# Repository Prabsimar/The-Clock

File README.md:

# The-Clock
A clock made using arduino and pcb designing

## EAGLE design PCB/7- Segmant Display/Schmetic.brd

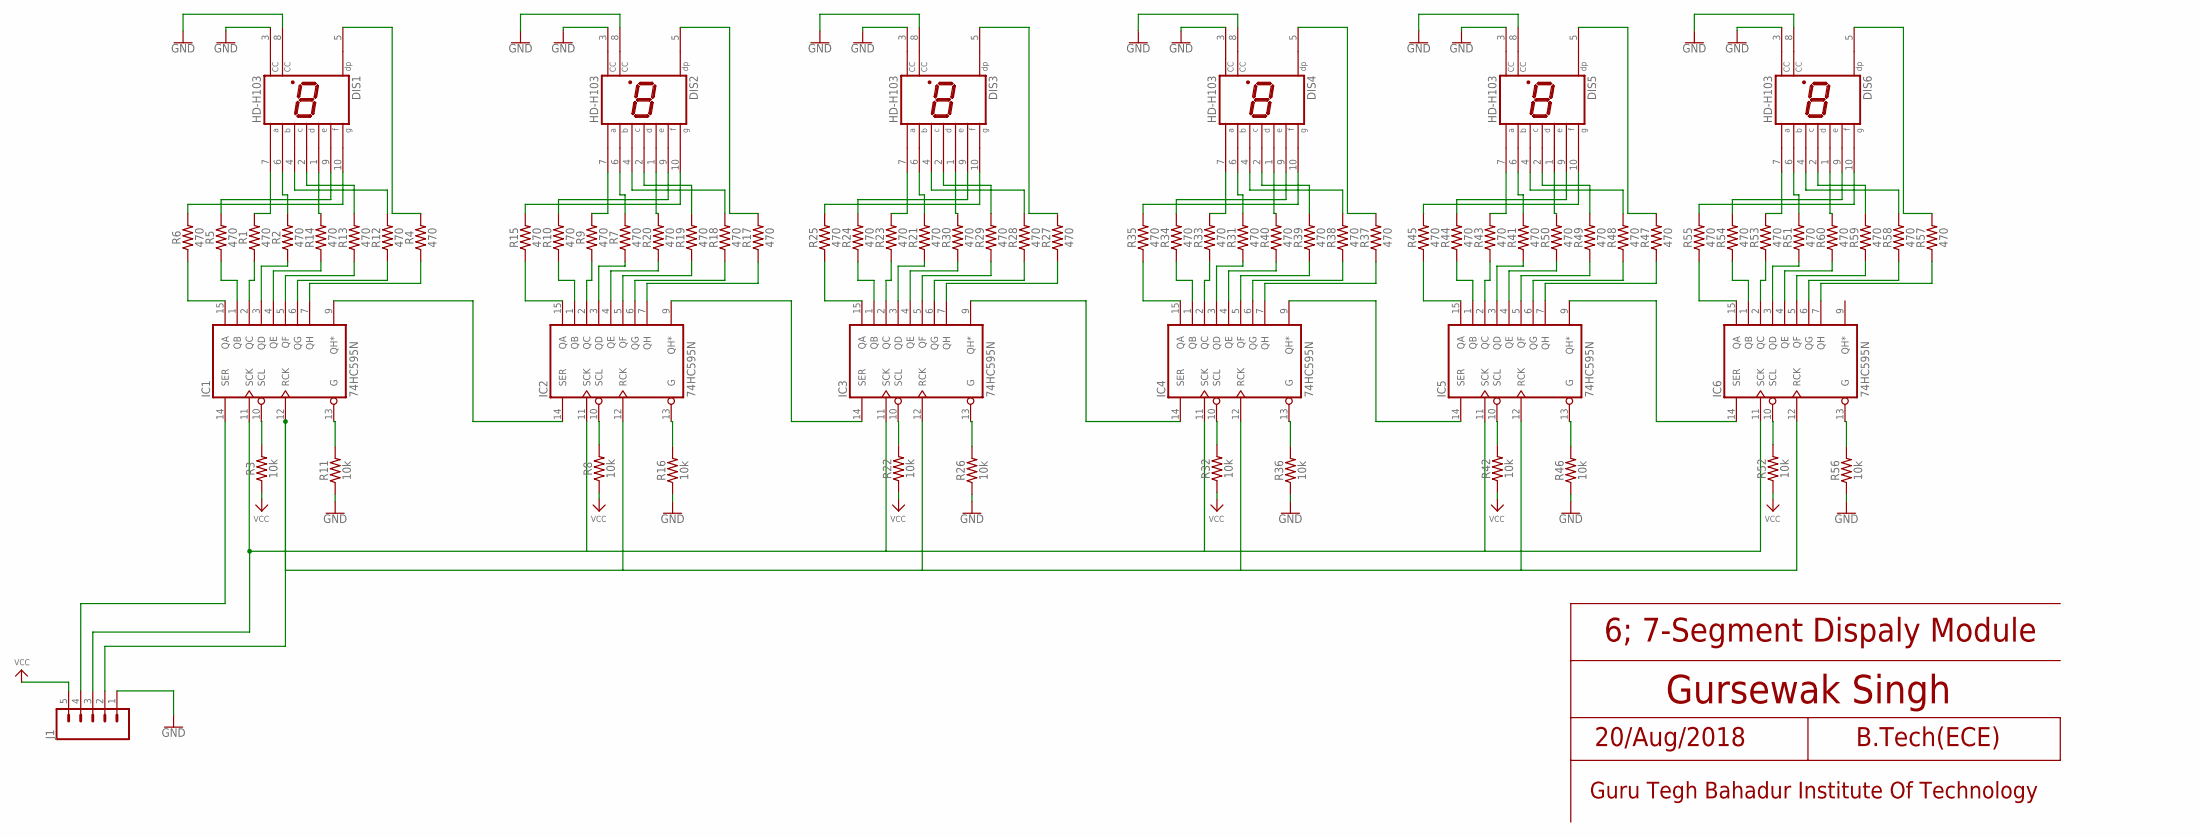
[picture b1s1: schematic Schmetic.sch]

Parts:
DIS1, DIS2, DIS3, DIS4, DIS5, DIS6: HD-H103; HDSP-M
IC1, IC2, IC3, IC4, IC5, IC6: 74HC595N; DIL16
J1: CONN_05LOCK_LONGPADS; 1X05_LOCK_LONGPADS
R1, R2, R4, R5, R6, R7, R9, R10, R12, R13, R14, R15, R17, R18, R19, R20, R21, R23, R24, R25, R27, R28, R29, R30, R31, R33, R34, R35, R37, R38, R39, R40, R41, R43, R44, R45, R47, R48, R49, R50, R51, R53, R54, R55, R57, R58, R59, R60: 470; AXIAL-0.3
R3, R8, R11, R16, R22, R26, R32, R36, R42, R46, R52, R56: 10k; AXIAL-0.3

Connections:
GND: DIS1.3 (CC), DIS1.8 (CC), DIS2.3 (CC), DIS2.8 (CC), DIS3.3 (CC), DIS3.8 (CC), DIS4.3 (CC), DIS4.8 (CC), DIS5.3 (CC), DIS5.8 (CC), DIS6.3 (CC), DIS6.8 (CC), IC1.8 (GND), IC2.8 (GND), IC3.8 (GND), IC4.8 (GND), IC5.8 (GND), IC6.8 (GND), J1.1, R11.P$1 (1), R16.P$1 (1), R26.P$1 (1), R36.P$1 (1), R46.P$1 (1), R56.P$1 (1)
unnamed: IC1.15 (QA), R6.P$1 (1)
unnamed: IC1.1 (QB), R5.P$1 (1)
unnamed: IC1.2 (QC), R1.P$1 (1)
unnamed: IC1.3 (QD), R2.P$1 (1)
unnamed: IC1.4 (QE), R14.P$1 (1)
unnamed: IC1.5 (QF), R13.P$1 (1)
unnamed: IC1.6 (QG), R12.P$1 (1)
unnamed: IC1.7 (QH), R4.P$1 (1)
unnamed: DIS1.10 (G), R6.P$2 (2)
unnamed: DIS1.9 (F), R5.P$2 (2)
unnamed: DIS1.7 (A), R1.P$2 (2)
unnamed: DIS1.6 (B), R2.P$2 (2)
unnamed: DIS1.1 (E), R14.P$2 (2)
unnamed: DIS1.2 (D), R13.P$2 (2)
unnamed: DIS1.4 (C), R12.P$2 (2)
unnamed: DIS1.5 (DP), R4.P$2 (2)
unnamed: IC2.15 (QA), R15.P$1 (1)
unnamed: IC1.10 (SCL), R3.P$2 (2)
unnamed: IC1.13 (G), R11.P$2 (2)
unnamed: IC2.1 (QB), R10.P$1 (1)
unnamed: IC2.2 (QC), R9.P$1 (1)
unnamed: IC2.3 (QD), R7.P$1 (1)
unnamed: IC2.4 (QE), R20.P$1 (1)
unnamed: IC2.5 (QF), R19.P$1 (1)
unnamed: IC2.6 (QG), R18.P$1 (1)
unnamed: IC2.7 (QH), R17.P$1 (1)
unnamed: DIS2.10 (G), R15.P$2 (2)
unnamed: DIS2.9 (F), R10.P$2 (2)
unnamed: DIS2.7 (A), R9.P$2 (2)
unnamed: DIS2.6 (B), R7.P$2 (2)
unnamed: DIS2.1 (E), R20.P$2 (2)
unnamed: DIS2.2 (D), R19.P$2 (2)
unnamed: DIS2.4 (C), R18.P$2 (2)
unnamed: DIS2.5 (DP), R17.P$2 (2)
unnamed: IC2.10 (SCL), R8.P$2 (2)
unnamed: IC2.13 (G), R16.P$2 (2)
unnamed: IC3.15 (QA), R25.P$1 (1)
unnamed: IC3.1 (QB), R24.P$1 (1)
unnamed: IC3.2 (QC), R23.P$1 (1)
unnamed: IC3.3 (QD), R21.P$1 (1)
unnamed: IC3.4 (QE), R30.P$1 (1)
unnamed: IC3.5 (QF), R29.P$1 (1)
unnamed: IC3.6 (QG), R28.P$1 (1)
unnamed: IC3.7 (QH), R27.P$1 (1)
unnamed: DIS3.10 (G), R25.P$2 (2)
unnamed: DIS3.9 (F), R24.P$2 (2)
unnamed: DIS3.7 (A), R23.P$2 (2)
unnamed: DIS3.6 (B), R21.P$2 (2)
unnamed: DIS3.1 (E), R30.P$2 (2)
unnamed: DIS3.2 (D), R29.P$2 (2)
unnamed: DIS3.4 (C), R28.P$2 (2)
unnamed: DIS3.5 (DP), R27.P$2 (2)
unnamed: IC3.10 (SCL), R22.P$2 (2)
unnamed: IC3.13 (G), R26.P$2 (2)
unnamed: IC4.15 (QA), R35.P$1 (1)
unnamed: IC4.1 (QB), R34.P$1 (1)
unnamed: IC4.2 (QC), R33.P$1 (1)
unnamed: IC4.3 (QD), R31.P$1 (1)
unnamed: IC4.4 (QE), R40.P$1 (1)
unnamed: IC4.5 (QF), R39.P$1 (1)
unnamed: IC4.6 (QG), R38.P$1 (1)
unnamed: IC4.7 (QH), R37.P$1 (1)
unnamed: DIS4.10 (G), R35.P$2 (2)
unnamed: DIS4.9 (F), R34.P$2 (2)
unnamed: DIS4.7 (A), R33.P$2 (2)
unnamed: DIS4.6 (B), R31.P$2 (2)
unnamed: DIS4.1 (E), R40.P$2 (2)
unnamed: DIS4.2 (D), R39.P$2 (2)
unnamed: DIS4.4 (C), R38.P$2 (2)
unnamed: DIS4.5 (DP), R37.P$2 (2)
unnamed: IC4.10 (SCL), R32.P$2 (2)
unnamed: IC4.13 (G), R36.P$2 (2)
unnamed: IC5.15 (QA), R45.P$1 (1)
unnamed: IC5.1 (QB), R44.P$1 (1)
unnamed: IC5.2 (QC), R43.P$1 (1)
unnamed: IC5.3 (QD), R41.P$1 (1)
unnamed: IC5.4 (QE), R50.P$1 (1)
unnamed: IC5.5 (QF), R49.P$1 (1)
unnamed: IC5.6 (QG), R48.P$1 (1)
unnamed: IC5.7 (QH), R47.P$1 (1)
unnamed: DIS5.10 (G), R45.P$2 (2)
unnamed: DIS5.9 (F), R44.P$2 (2)
unnamed: DIS5.7 (A), R43.P$2 (2)
unnamed: DIS5.6 (B), R41.P$2 (2)
unnamed: DIS5.1 (E), R50.P$2 (2)
unnamed: DIS5.2 (D), R49.P$2 (2)
unnamed: DIS5.4 (C), R48.P$2 (2)
unnamed: DIS5.5 (DP), R47.P$2 (2)
unnamed: IC5.10 (SCL), R42.P$2 (2)
unnamed: IC5.13 (G), R46.P$2 (2)
unnamed: IC6.15 (QA), R55.P$1 (1)
unnamed: IC6.1 (QB), R54.P$1 (1)
unnamed: IC6.2 (QC), R53.P$1 (1)
unnamed: IC6.3 (QD), R51.P$1 (1)
unnamed: IC6.4 (QE), R60.P$1 (1)
unnamed: IC6.5 (QF), R59.P$1 (1)
unnamed: IC6.6 (QG), R58.P$1 (1)
unnamed: IC6.7 (QH), R57.P$1 (1)
unnamed: DIS6.10 (G), R55.P$2 (2)
unnamed: DIS6.9 (F), R54.P$2 (2)
unnamed: DIS6.7 (A), R53.P$2 (2)
unnamed: DIS6.6 (B), R51.P$2 (2)
unnamed: DIS6.1 (E), R60.P$2 (2)
unnamed: DIS6.2 (D), R59.P$2 (2)
unnamed: DIS6.4 (C), R58.P$2 (2)
unnamed: DIS6.5 (DP), R57.P$2 (2)
unnamed: IC6.10 (SCL), R52.P$2 (2)
unnamed: IC6.13 (G), R56.P$2 (2)
unnamed: IC1.9 (QH*), IC2.14 (SER)
unnamed: IC2.9 (QH*), IC3.14 (SER)
unnamed: IC3.9 (QH*), IC4.14 (SER)
unnamed: IC4.9 (QH*), IC5.14 (SER)
unnamed: IC5.9 (QH*), IC6.14 (SER)
unnamed: IC1.11 (SCK), IC2.11 (SCK), IC3.11 (SCK), IC4.11 (SCK), IC5.11 (SCK), IC6.11 (SCK), J1.3
unnamed: IC1.12 (RCK), IC2.12 (RCK), IC3.12 (RCK), IC4.12 (RCK), IC5.12 (RCK), IC6.12 (RCK), J1.2
unnamed: IC1.14 (SER), J1.4
VCC: IC1.16 (VCC), IC2.16 (VCC), IC3.16 (VCC), IC4.16 (VCC), IC5.16 (VCC), IC6.16 (VCC), J1.5, R3.P$1 (1), R8.P$1 (1), R22.P$1 (1), R32.P$1 (1), R42.P$1 (1), R52.P$1 (1)

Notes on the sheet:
6; 7-Segment Dispaly Module
Gursewak Singh
20/Aug/2018
B.Tech(ECE)
Guru Tegh Bahadur Institute Of Technology

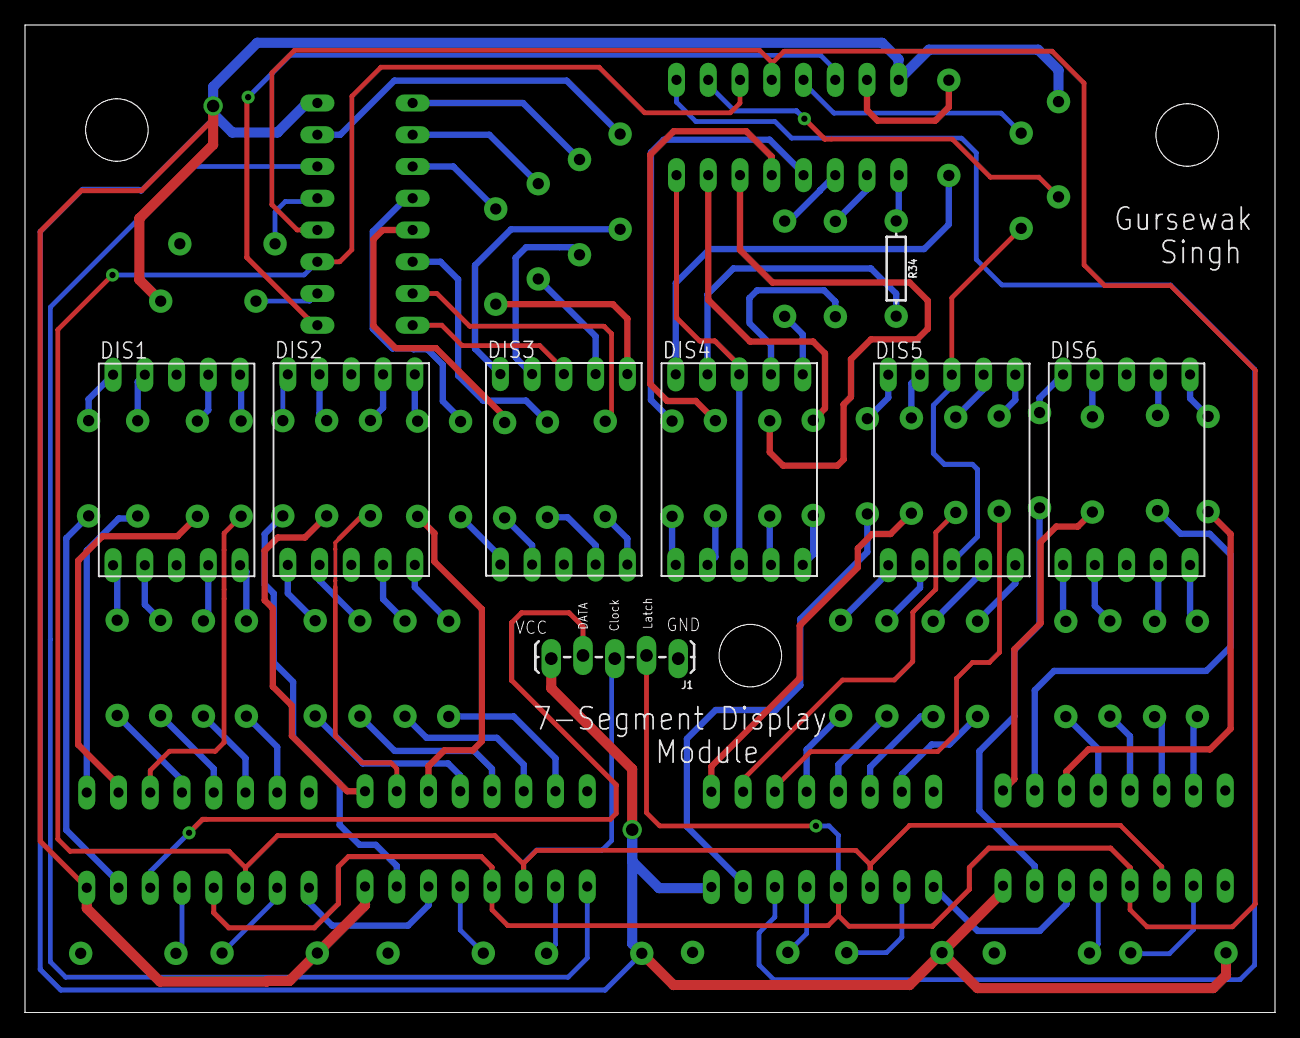
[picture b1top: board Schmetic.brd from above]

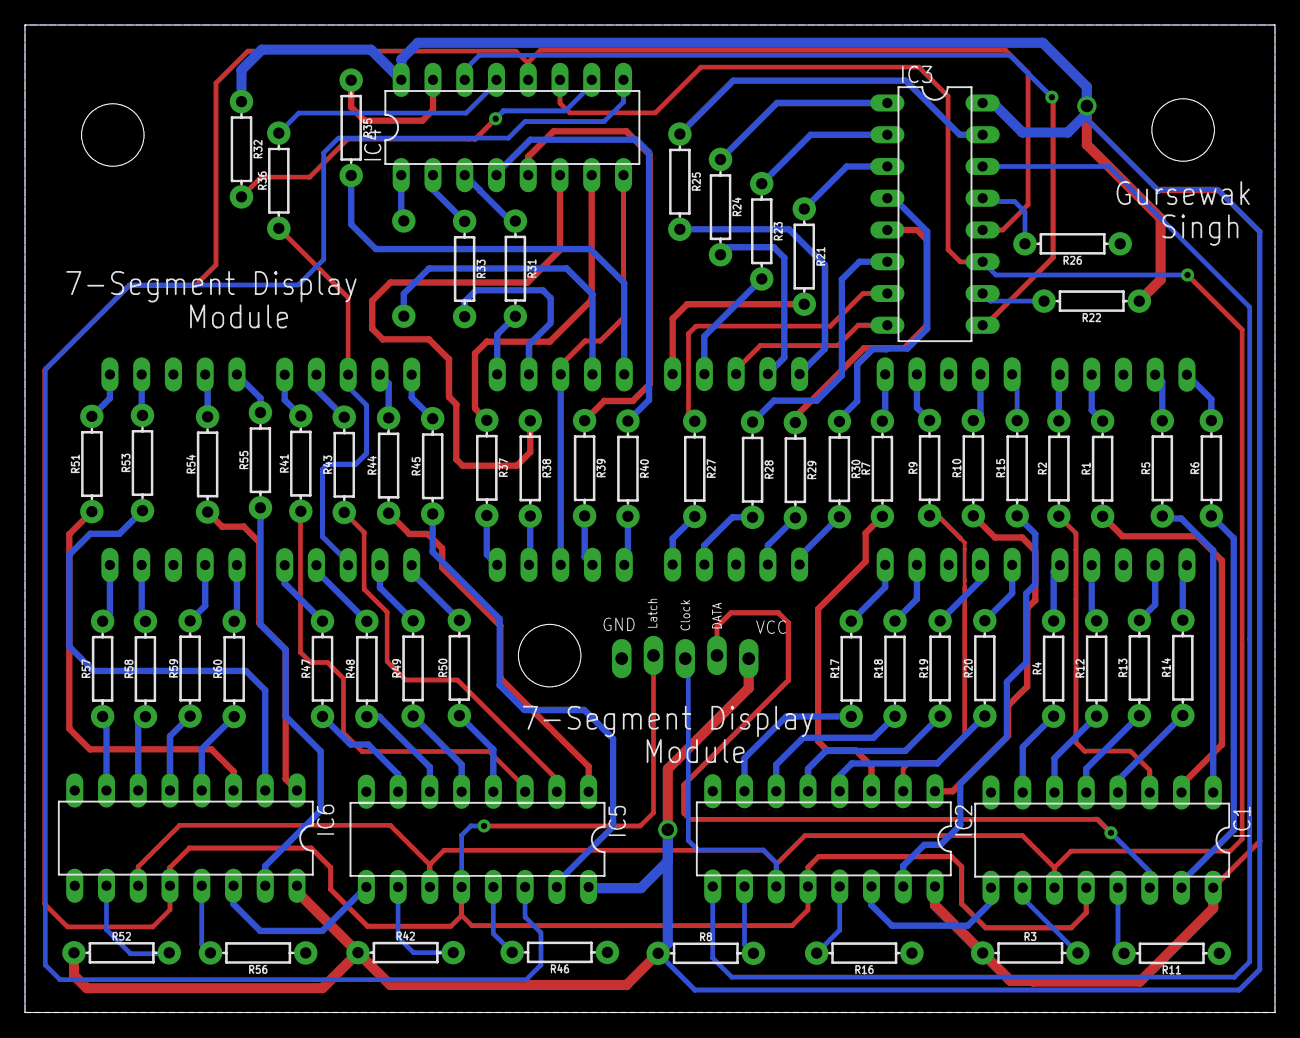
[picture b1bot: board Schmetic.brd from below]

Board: 2 copper layers, 100.0 x 79.0 mm, 73 parts (65 on the bottom side), 118 nets.

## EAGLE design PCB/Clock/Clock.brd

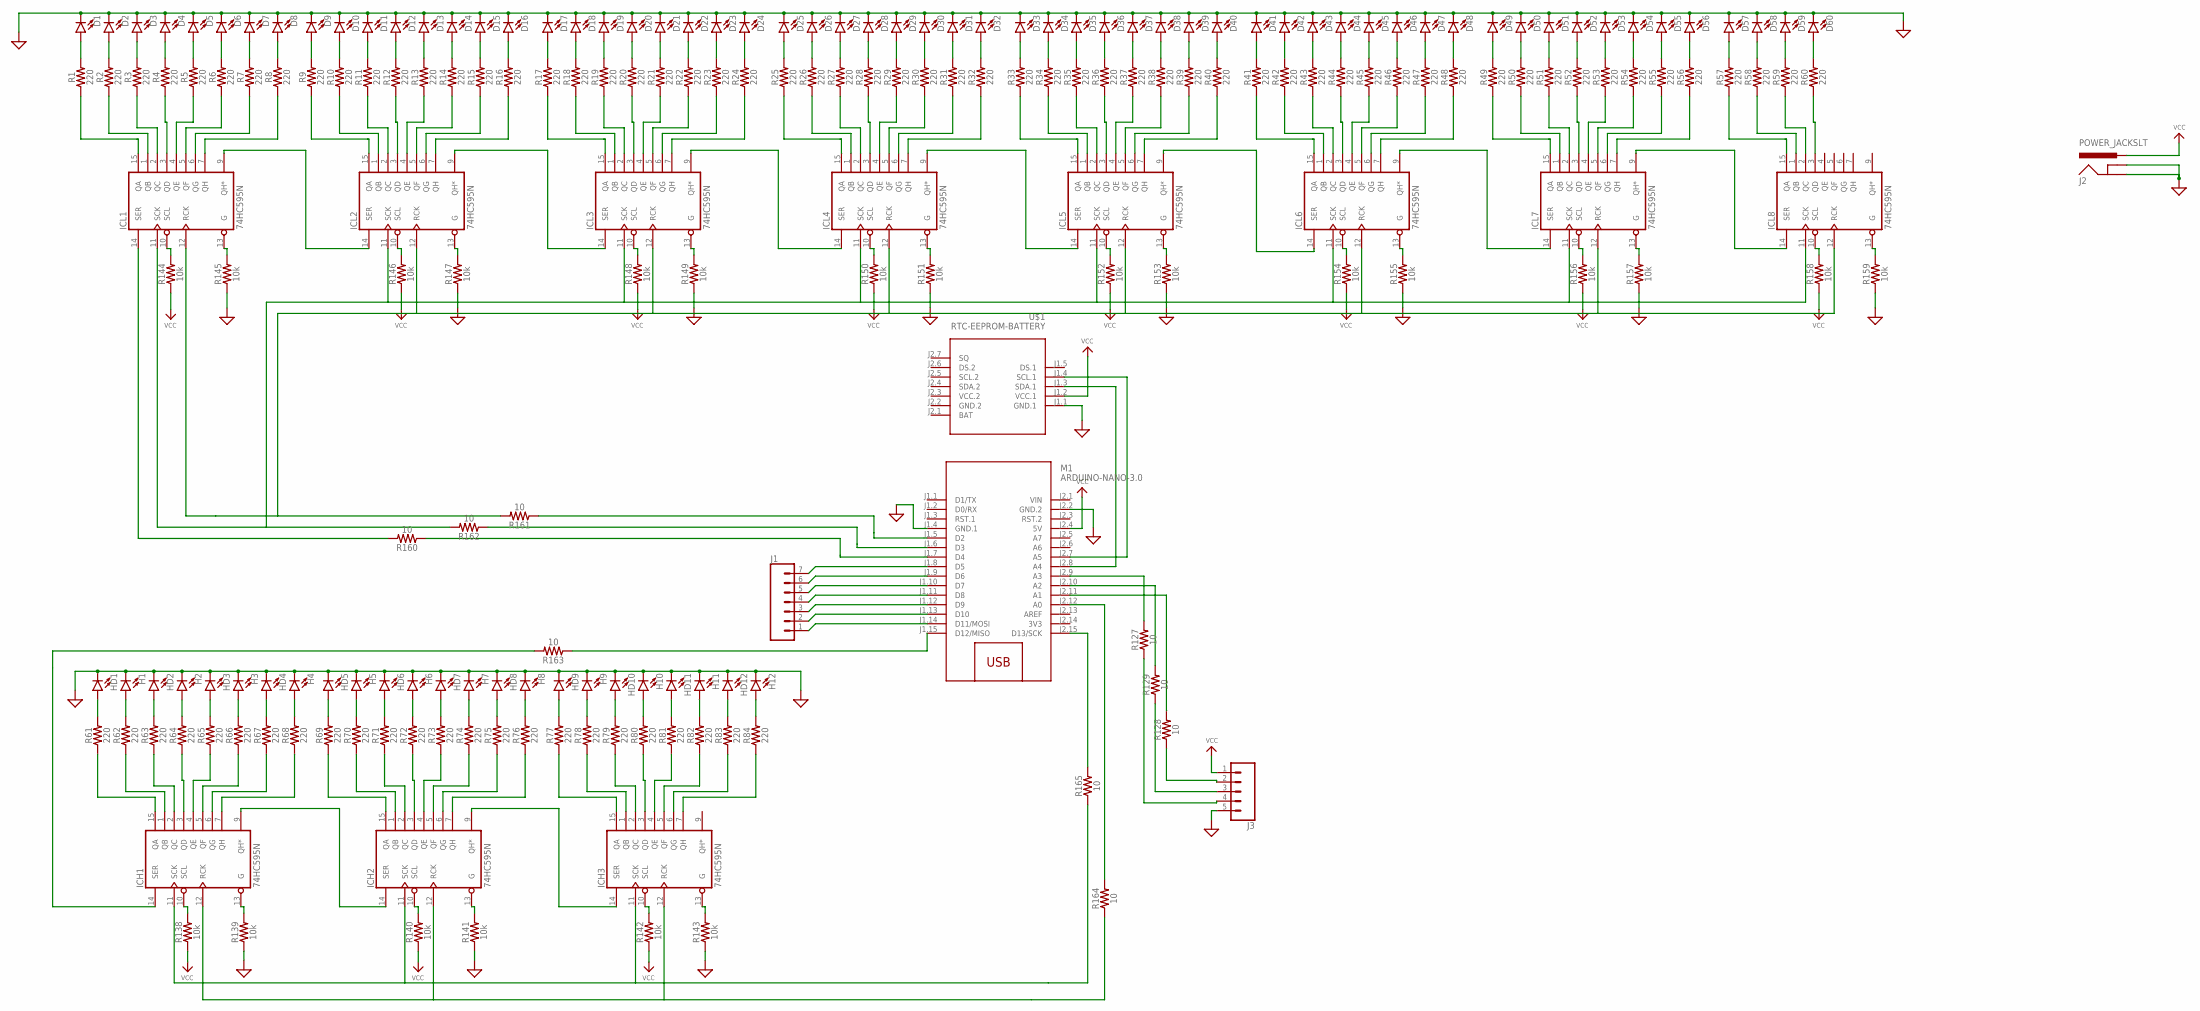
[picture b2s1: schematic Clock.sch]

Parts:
D1, D2, D3, D4, D5, D6, D7, D8, D9, D10, D11, D12, D13, D14, D15, D16, D17, D18, D19, D20, D21, D22, D23, D24, D25, D26, D27, D28, D29, D30, D31, D32, D33, D34, D35, D36, D37, D38, D39, D40, D41, D42, D43, D44, D45, D46, D47, D48, D49, D50, D51, D52, D53, D54, D55, D56, D57, D58, D59, D60: LED5MM; LED_5MM
H1, H2, H3, H4, H5, H6, H7, H8, H9, H10, H11, H12: LED5MM; LED_5MM
HD1, HD2, HD3, HD4, HD5, HD6, HD7, HD8, HD9, HD10, HD11, HD12: LED5MM; LED_5MM
ICH1, ICH2, ICH3: 74HC595N; DIL16
ICL1, ICL2, ICL3, ICL4, ICL5, ICL6, ICL7, ICL8: 74HC595N; DIL16
J1: CONN_07LOCK_LONGPADS; 1X07_LOCK_LONGPADS
J2: POWER_JACKSLT; POWER_JACK_SLOT
J3: CONN_05LOCK_LONGPADS; 1X05_LOCK_LONGPADS
M1: ARDUINO-NANO-3.0
R1, R2, R3, R4, R5, R6, R7, R8, R9, R10, R11, R12, R13, R14, R15, R16, R17, R18, R19, R20, R21, R22, R23, R24, R25, R26, R27, R28, R29, R30, R31, R32, R33, R34, R35, R36, R37, R38, R39, R40, R41, R42, R43, R44, R45, R46, R47, R48, R49, R50, R51, R52, R53, R54, R55, R56, R57, R58, R59, R60, R61, R62, R63, R64, R65, R66, R67, R68, R69, R70, R71, R72, R73, R74, R75, R76, R77, R78, R79, R80, R81, R82, R83, R84: 220; AXIAL-0.3
R127, R128, R129, R160, R161, R162, R163, R164, R165: 10; AXIAL-0.3
R138, R139, R140, R141, R142, R143, R144, R145, R146, R147, R148, R149, R150, R151, R152, R153, R154, R155, R156, R157, R158, R159: 10k; AXIAL-0.3
U$1: RTC-EEPROM-BATTERY

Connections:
3V3: M1.J2.14 (3V3)
GND: D1.K (C), D2.K (C), D3.K (C), D4.K (C), D5.K (C), D6.K (C), D7.K (C), D8.K (C), D9.K (C), D10.K (C), D11.K (C), D12.K (C), D13.K (C), D14.K (C), D15.K (C), D16.K (C), D17.K (C), D18.K (C), D19.K (C), D20.K (C), D21.K (C), D22.K (C), D23.K (C), D24.K (C), D25.K (C), D26.K (C), D27.K (C), D28.K (C), D29.K (C), D30.K (C), D31.K (C), D32.K (C), D33.K (C), D34.K (C), D35.K (C), D36.K (C), D37.K (C), D38.K (C), D39.K (C), D40.K (C), D41.K (C), D42.K (C), D43.K (C), D44.K (C), D45.K (C), D46.K (C), D47.K (C), D48.K (C), D49.K (C), D50.K (C), D51.K (C), D52.K (C), D53.K (C), D54.K (C), D55.K (C), D56.K (C), D57.K (C), D58.K (C), D59.K (C), D60.K (C), H1.K (C), H2.K (C), H3.K (C), H4.K (C), H5.K (C), H6.K (C), H7.K (C), H8.K (C), H9.K (C), H10.K (C), H11.K (C), H12.K (C), HD1.K (C), HD2.K (C), HD3.K (C), HD4.K (C), HD5.K (C), HD6.K (C), HD7.K (C), HD8.K (C), HD9.K (C), HD10.K (C), HD11.K (C), HD12.K (C), ICH1.8 (GND), ICH2.8 (GND), ICH3.8 (GND), ICL1.8 (GND), ICL2.8 (GND), ICL3.8 (GND), ICL4.8 (GND), ICL5.8 (GND), ICL6.8 (GND), ICL7.8 (GND), ICL8.8 (GND), J2.GND@1 (GNDBREAK), J2.GND@2 (GND), J3.5, M1.J1.4 (GND.1), M1.J2.2 (GND.2), R139.P$1 (1), R141.P$1 (1), R143.P$1 (1), R145.P$1 (1), R147.P$1 (1), R149.P$1 (1), R151.P$1 (1), R153.P$1 (1), R155.P$1 (1), R157.P$1 (1), R159.P$1 (1), U$1.J1.1 (GND.1)
GND.2: U$1.J2.2 (GND.2)
unnamed: M1.J2.7 (A5), U$1.J1.4 (SCL.1)
unnamed: M1.J2.8 (A4), U$1.J1.3 (SDA.1)
unnamed: J1.7, M1.J1.8 (D5)
unnamed: J1.6, M1.J1.9 (D6)
unnamed: J1.5, M1.J1.10 (D7)
unnamed: J1.4, M1.J1.11 (D8)
unnamed: J1.3, M1.J1.12 (D9)
unnamed: J1.2, M1.J1.13 (D10)
unnamed: J1.1, M1.J1.14 (D11/MOSI)
unnamed: ICL1.5 (QF), R6.P$1 (1)
unnamed: ICL1.7 (QH), R8.P$1 (1)
unnamed: ICL1.3 (QD), R4.P$1 (1)
unnamed: ICL1.4 (QE), R5.P$1 (1)
unnamed: ICL1.2 (QC), R3.P$1 (1)
unnamed: ICL1.1 (QB), R2.P$1 (1)
unnamed: ICL1.6 (QG), R7.P$1 (1)
unnamed: ICH1.6 (QG), R67.P$1 (1)
unnamed: D1.A, R1.P$2 (2)
unnamed: D2.A, R2.P$2 (2)
unnamed: D3.A, R3.P$2 (2)
unnamed: D4.A, R4.P$2 (2)
unnamed: D5.A, R5.P$2 (2)
unnamed: D6.A, R6.P$2 (2)
unnamed: D7.A, R7.P$2 (2)
unnamed: D8.A, R8.P$2 (2)
unnamed: ICL1.15 (QA), R1.P$1 (1)
unnamed: ICL2.6 (QG), R15.P$1 (1)
unnamed: D9.A, R9.P$2 (2)
unnamed: D10.A, R10.P$2 (2)
unnamed: D11.A, R11.P$2 (2)
unnamed: D12.A, R12.P$2 (2)
unnamed: D13.A, R13.P$2 (2)
unnamed: D14.A, R14.P$2 (2)
unnamed: D15.A, R15.P$2 (2)
unnamed: D16.A, R16.P$2 (2)
unnamed: ICL2.7 (QH), R16.P$1 (1)
unnamed: ICL2.15 (QA), R9.P$1 (1)
unnamed: ICL2.5 (QF), R14.P$1 (1)
unnamed: ICL2.2 (QC), R11.P$1 (1)
unnamed: ICL2.1 (QB), R10.P$1 (1)
unnamed: ICL2.3 (QD), R12.P$1 (1)
unnamed: ICL2.4 (QE), R13.P$1 (1)
unnamed: ICL1.14 (SER), R160.P$2 (2)
unnamed: ICL3.6 (QG), R23.P$1 (1)
unnamed: D17.A, R17.P$2 (2)
unnamed: D18.A, R18.P$2 (2)
unnamed: D19.A, R19.P$2 (2)
unnamed: D20.A, R20.P$2 (2)
unnamed: D21.A, R21.P$2 (2)
unnamed: D22.A, R22.P$2 (2)
unnamed: D23.A, R23.P$2 (2)
unnamed: D24.A, R24.P$2 (2)
unnamed: ICL3.7 (QH), R24.P$1 (1)
unnamed: ICL3.15 (QA), R17.P$1 (1)
unnamed: ICL3.5 (QF), R22.P$1 (1)
unnamed: ICL3.2 (QC), R19.P$1 (1)
unnamed: ICL3.1 (QB), R18.P$1 (1)
unnamed: ICL3.3 (QD), R20.P$1 (1)
unnamed: ICL3.4 (QE), R21.P$1 (1)
unnamed: HD1.A, R61.P$2 (2)
unnamed: ICL4.6 (QG), R31.P$1 (1)
unnamed: D25.A, R25.P$2 (2)
unnamed: D26.A, R26.P$2 (2)
unnamed: D27.A, R27.P$2 (2)
unnamed: D28.A, R28.P$2 (2)
unnamed: D29.A, R29.P$2 (2)
unnamed: D30.A, R30.P$2 (2)
unnamed: D31.A, R31.P$2 (2)
unnamed: D32.A, R32.P$2 (2)
unnamed: ICL4.7 (QH), R32.P$1 (1)
unnamed: ICL4.15 (QA), R25.P$1 (1)
unnamed: ICL4.5 (QF), R30.P$1 (1)
unnamed: ICL4.2 (QC), R27.P$1 (1)
unnamed: ICL4.1 (QB), R26.P$1 (1)
unnamed: ICL4.3 (QD), R28.P$1 (1)
unnamed: ICL4.4 (QE), R29.P$1 (1)
unnamed: ICL1.12 (RCK), ICL2.12 (RCK), ICL3.12 (RCK), ICL4.12 (RCK), ICL5.12 (RCK), ICL6.12 (RCK), ICL7.12 (RCK), ICL8.12 (RCK), R161.P$2 (2)
unnamed: ICL5.6 (QG), R39.P$1 (1)
unnamed: D33.A, R33.P$2 (2)
unnamed: D34.A, R34.P$2 (2)
unnamed: D35.A, R35.P$2 (2)
unnamed: D36.A, R36.P$2 (2)
unnamed: D37.A, R37.P$2 (2)
unnamed: D38.A, R38.P$2 (2)
unnamed: D39.A, R39.P$2 (2)
unnamed: D40.A, R40.P$2 (2)
unnamed: ICL5.7 (QH), R40.P$1 (1)
unnamed: ICL5.15 (QA), R33.P$1 (1)
unnamed: ICL5.5 (QF), R38.P$1 (1)
unnamed: ICL5.2 (QC), R35.P$1 (1)
unnamed: ICL5.1 (QB), R34.P$1 (1)
unnamed: ICL5.3 (QD), R36.P$1 (1)
unnamed: ICL5.4 (QE), R37.P$1 (1)
unnamed: ICL1.9 (QH*), ICL2.14 (SER)
unnamed: ICL6.6 (QG), R47.P$1 (1)
unnamed: D41.A, R41.P$2 (2)
unnamed: D42.A, R42.P$2 (2)
unnamed: D43.A, R43.P$2 (2)
unnamed: D44.A, R44.P$2 (2)
unnamed: D45.A, R45.P$2 (2)
unnamed: D46.A, R46.P$2 (2)
unnamed: D47.A, R47.P$2 (2)
unnamed: D48.A, R48.P$2 (2)
unnamed: ICL6.7 (QH), R48.P$1 (1)
unnamed: ICL6.15 (QA), R41.P$1 (1)
unnamed: ICL6.5 (QF), R46.P$1 (1)
unnamed: ICL6.2 (QC), R43.P$1 (1)
unnamed: ICL6.1 (QB), R42.P$1 (1)
unnamed: ICL6.3 (QD), R44.P$1 (1)
unnamed: ICL6.4 (QE), R45.P$1 (1)
unnamed: ICL2.9 (QH*), ICL3.14 (SER)
unnamed: ICL7.6 (QG), R55.P$1 (1)
unnamed: D49.A, R49.P$2 (2)
unnamed: D50.A, R50.P$2 (2)
unnamed: D51.A, R51.P$2 (2)
unnamed: D52.A, R52.P$2 (2)
unnamed: D53.A, R53.P$2 (2)
unnamed: D54.A, R54.P$2 (2)
unnamed: D55.A, R55.P$2 (2)
unnamed: D56.A, R56.P$2 (2)
unnamed: ICL7.7 (QH), R56.P$1 (1)
unnamed: ICL7.15 (QA), R49.P$1 (1)
unnamed: ICL7.5 (QF), R54.P$1 (1)
unnamed: ICL7.2 (QC), R51.P$1 (1)
unnamed: ICL7.1 (QB), R50.P$1 (1)
unnamed: ICL7.3 (QD), R52.P$1 (1)
unnamed: ICL7.4 (QE), R53.P$1 (1)
unnamed: ICL3.9 (QH*), ICL4.14 (SER)
unnamed: ICL4.9 (QH*), ICL5.14 (SER)
unnamed: D57.A, R57.P$2 (2)
unnamed: D58.A, R58.P$2 (2)
unnamed: D59.A, R59.P$2 (2)
unnamed: D60.A, R60.P$2 (2)
unnamed: ICL5.9 (QH*), ICL6.14 (SER)
unnamed: ICL6.9 (QH*), ICL7.14 (SER)
unnamed: ICL7.9 (QH*), ICL8.14 (SER)
unnamed: ICL1.11 (SCK), ICL2.11 (SCK), ICL3.11 (SCK), ICL4.11 (SCK), ICL5.11 (SCK), ICL6.11 (SCK), ICL7.11 (SCK), ICL8.11 (SCK), R162.P$2 (2)
unnamed: H1.A, R62.P$2 (2)
unnamed: ICL8.15 (QA), R57.P$1 (1)
unnamed: HD2.A, R63.P$2 (2)
unnamed: ICL8.2 (QC), R59.P$1 (1)
unnamed: ICL8.1 (QB), R58.P$1 (1)
unnamed: ICL8.3 (QD), R60.P$1 (1)
unnamed: H2.A, R64.P$2 (2)
unnamed: HD3.A, R65.P$2 (2)
unnamed: H3.A, R66.P$2 (2)
unnamed: HD4.A, R67.P$2 (2)
unnamed: H4.A, R68.P$2 (2)
unnamed: ICH1.7 (QH), R68.P$1 (1)
unnamed: ICH1.15 (QA), R61.P$1 (1)
unnamed: ICH1.5 (QF), R66.P$1 (1)
unnamed: ICH1.2 (QC), R63.P$1 (1)
unnamed: ICH1.1 (QB), R62.P$1 (1)
unnamed: ICH1.3 (QD), R64.P$1 (1)
unnamed: ICH1.4 (QE), R65.P$1 (1)
unnamed: ICH2.6 (QG), R75.P$1 (1)
unnamed: HD5.A, R69.P$2 (2)
unnamed: H5.A, R70.P$2 (2)
unnamed: HD6.A, R71.P$2 (2)
unnamed: H6.A, R72.P$2 (2)
unnamed: HD7.A, R73.P$2 (2)
unnamed: H7.A, R74.P$2 (2)
unnamed: HD8.A, R75.P$2 (2)
unnamed: H8.A, R76.P$2 (2)
unnamed: ICH2.7 (QH), R76.P$1 (1)
unnamed: ICH2.15 (QA), R69.P$1 (1)
unnamed: ICH2.5 (QF), R74.P$1 (1)
unnamed: ICH2.2 (QC), R71.P$1 (1)
unnamed: ICH2.1 (QB), R70.P$1 (1)
unnamed: ICH2.3 (QD), R72.P$1 (1)
unnamed: ICH2.4 (QE), R73.P$1 (1)
unnamed: ICH3.6 (QG), R83.P$1 (1)
unnamed: HD9.A, R77.P$2 (2)
unnamed: H9.A, R78.P$2 (2)
unnamed: HD10.A, R79.P$2 (2)
unnamed: H10.A, R80.P$2 (2)
unnamed: HD11.A, R81.P$2 (2)
unnamed: H11.A, R82.P$2 (2)
unnamed: HD12.A, R83.P$2 (2)
unnamed: H12.A, R84.P$2 (2)
unnamed: ICH3.7 (QH), R84.P$1 (1)
unnamed: ICH3.15 (QA), R77.P$1 (1)
unnamed: ICH3.5 (QF), R82.P$1 (1)
unnamed: ICH3.2 (QC), R79.P$1 (1)
unnamed: ICH3.1 (QB), R78.P$1 (1)
unnamed: ICH3.3 (QD), R80.P$1 (1)
unnamed: ICH3.4 (QE), R81.P$1 (1)
unnamed: ICH1.14 (SER), R163.P$2 (2)
unnamed: ICH1.11 (SCK), ICH2.11 (SCK), ICH3.11 (SCK), R165.P$1 (1)
unnamed: ICH1.12 (RCK), ICH2.12 (RCK), ICH3.12 (RCK), R164.P$1 (1)
unnamed: ICH1.9 (QH*), ICH2.14 (SER)
unnamed: ICH2.9 (QH*), ICH3.14 (SER)
unnamed: M1.J2.9 (A3), R127.P$2 (2)
unnamed: ICH1.10 (SCL), R138.P$2 (2)
unnamed: ICH1.13 (G), R139.P$2 (2)
unnamed: ICH2.10 (SCL), R140.P$2 (2)
unnamed: ICH2.13 (G), R141.P$2 (2)
unnamed: ICH3.10 (SCL), R142.P$2 (2)
unnamed: ICH3.13 (G), R143.P$2 (2)
unnamed: ICL1.10 (SCL), R144.P$2 (2)
unnamed: ICL1.13 (G), R145.P$2 (2)
unnamed: ICL2.10 (SCL), R146.P$2 (2)
unnamed: ICL2.13 (G), R147.P$2 (2)
unnamed: ICL3.10 (SCL), R148.P$2 (2)
unnamed: ICL3.13 (G), R149.P$2 (2)
unnamed: ICL4.10 (SCL), R150.P$2 (2)
unnamed: ICL4.13 (G), R151.P$2 (2)
unnamed: ICL5.10 (SCL), R152.P$2 (2)
unnamed: ICL5.13 (G), R153.P$2 (2)
unnamed: ICL6.10 (SCL), R154.P$2 (2)
unnamed: ICL6.13 (G), R155.P$2 (2)
unnamed: ICL7.10 (SCL), R156.P$2 (2)
unnamed: ICL7.13 (G), R157.P$2 (2)
unnamed: ICL8.10 (SCL), R158.P$2 (2)
unnamed: ICL8.13 (G), R159.P$2 (2)
unnamed: M1.J1.15 (D12/MISO), R163.P$1 (1)
unnamed: M1.J2.10 (A2), R129.P$2 (2)
unnamed: M1.J2.11 (A1), R128.P$2 (2)
unnamed: M1.J2.15 (D13/SCK), R165.P$2 (2)
unnamed: M1.J2.12 (A0), R164.P$2 (2)
unnamed: M1.J1.7 (D4), R160.P$1 (1)
unnamed: M1.J1.6 (D3), R162.P$1 (1)
unnamed: M1.J1.5 (D2), R161.P$1 (1)
unnamed: J3.4, R127.P$1 (1)
unnamed: J3.2, R128.P$1 (1)
unnamed: J3.3, R129.P$1 (1)
VCC: ICH1.16 (VCC), ICH2.16 (VCC), ICH3.16 (VCC), ICL1.16 (VCC), ICL2.16 (VCC), ICL3.16 (VCC), ICL4.16 (VCC), ICL5.16 (VCC), ICL6.16 (VCC), ICL7.16 (VCC), ICL8.16 (VCC), J2.PWR, J3.1, M1.J2.4 (5V), R138.P$1 (1), R140.P$1 (1), R142.P$1 (1), R144.P$1 (1), R146.P$1 (1), R148.P$1 (1), R150.P$1 (1), R152.P$1 (1), R154.P$1 (1), R156.P$1 (1), R158.P$1 (1), U$1.J1.2 (VCC.1)
VCC.2: U$1.J2.3 (VCC.2)
VIN: M1.J2.1 (VIN)

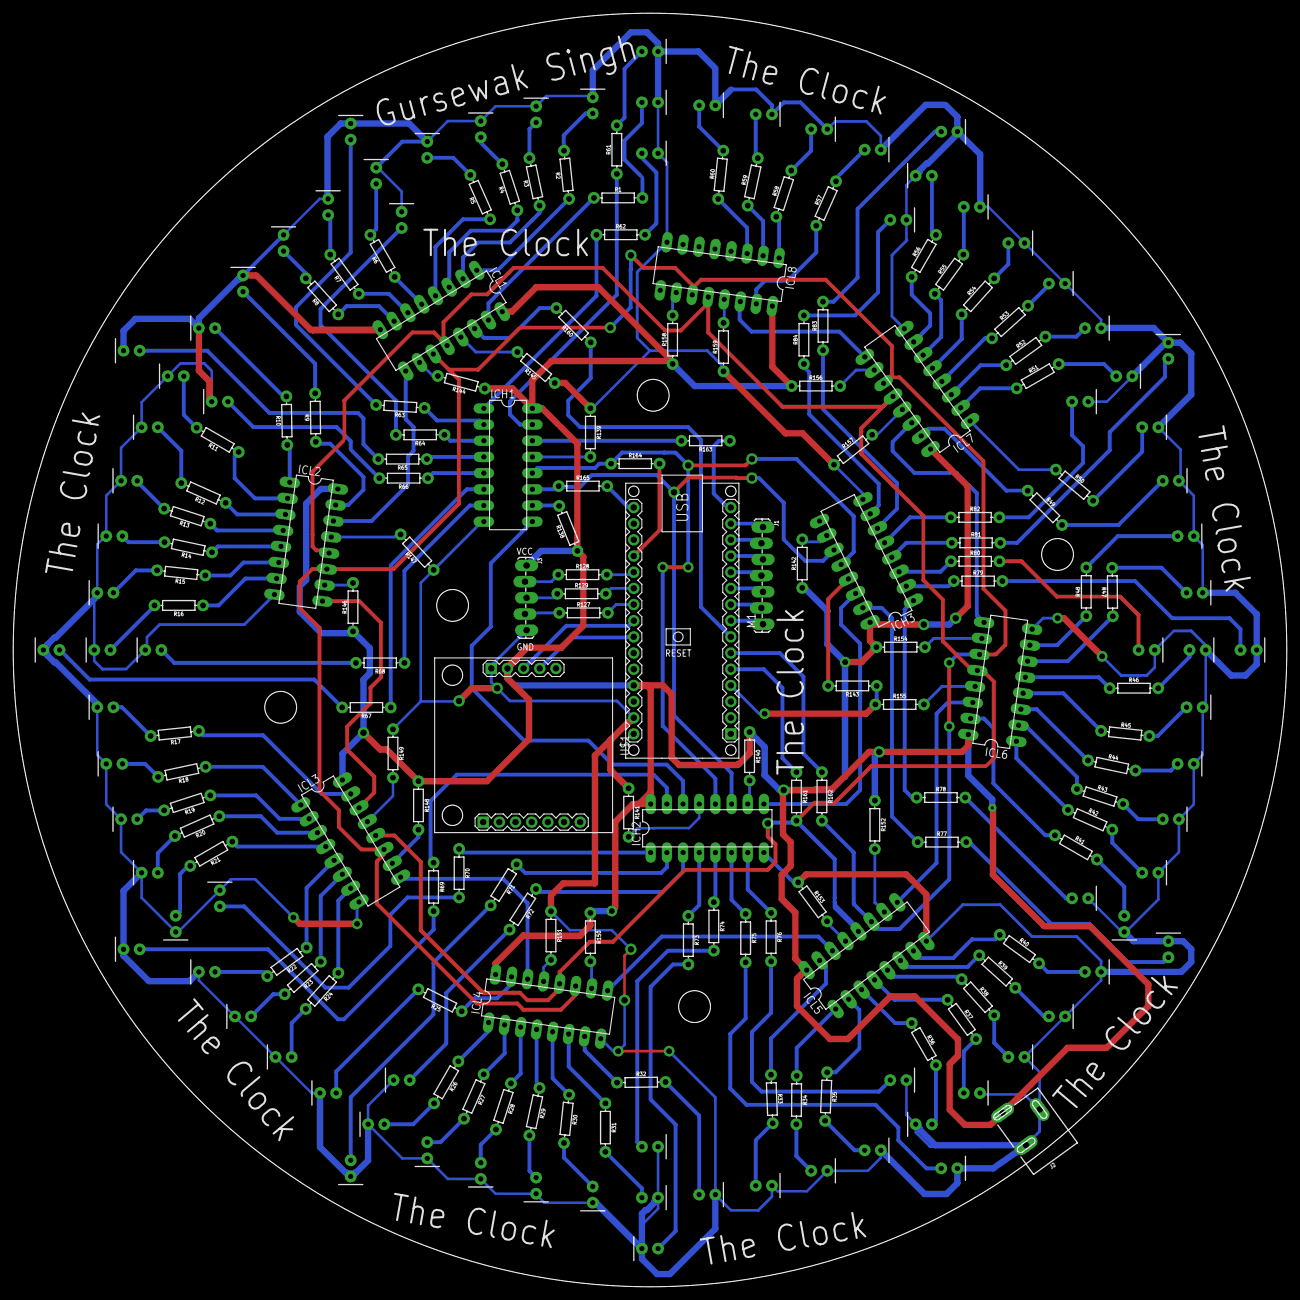
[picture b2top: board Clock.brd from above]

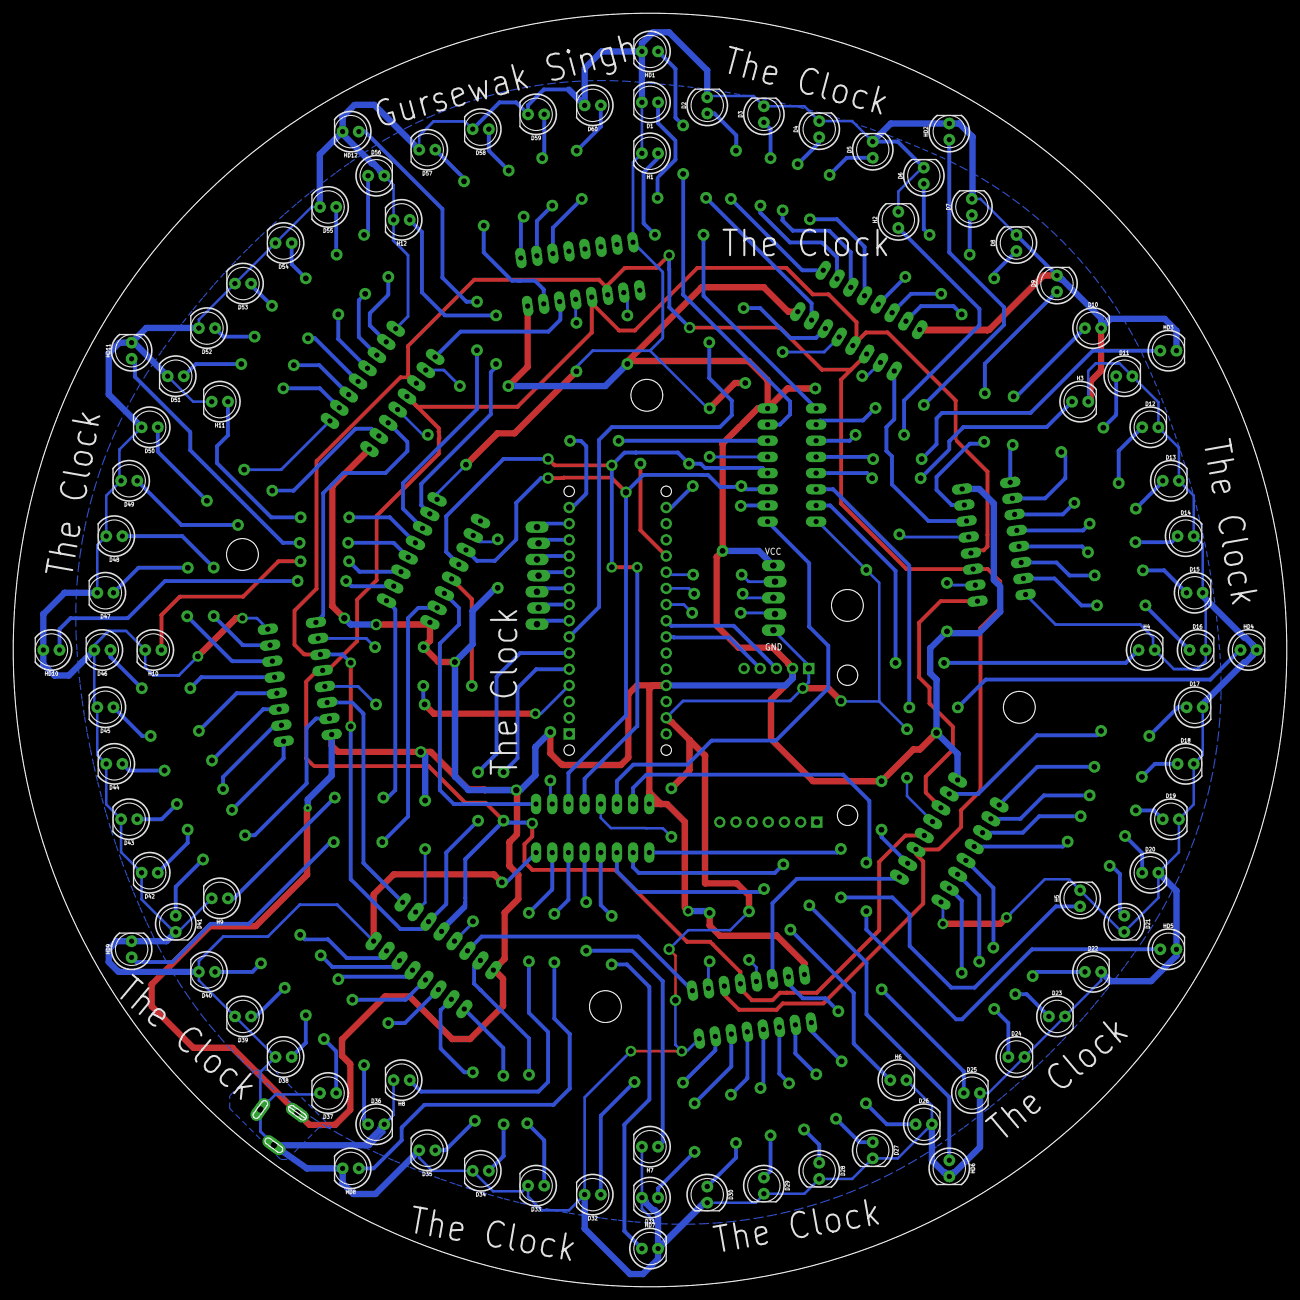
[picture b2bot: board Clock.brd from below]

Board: 2 copper layers, 200.0 x 200.0 mm, 215 parts (84 on the bottom side), 228 nets.

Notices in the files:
parts and their libraries:
SparkFun-Connectors: Licensing: Creative Commons ShareAlike 4.0 International - https://creativecommons.org/licenses/by-sa/4.0
diy-modules: Released under the Creative Commons Attribution 4.0 International License: http://creativecommons.org/licenses/by/4.0
